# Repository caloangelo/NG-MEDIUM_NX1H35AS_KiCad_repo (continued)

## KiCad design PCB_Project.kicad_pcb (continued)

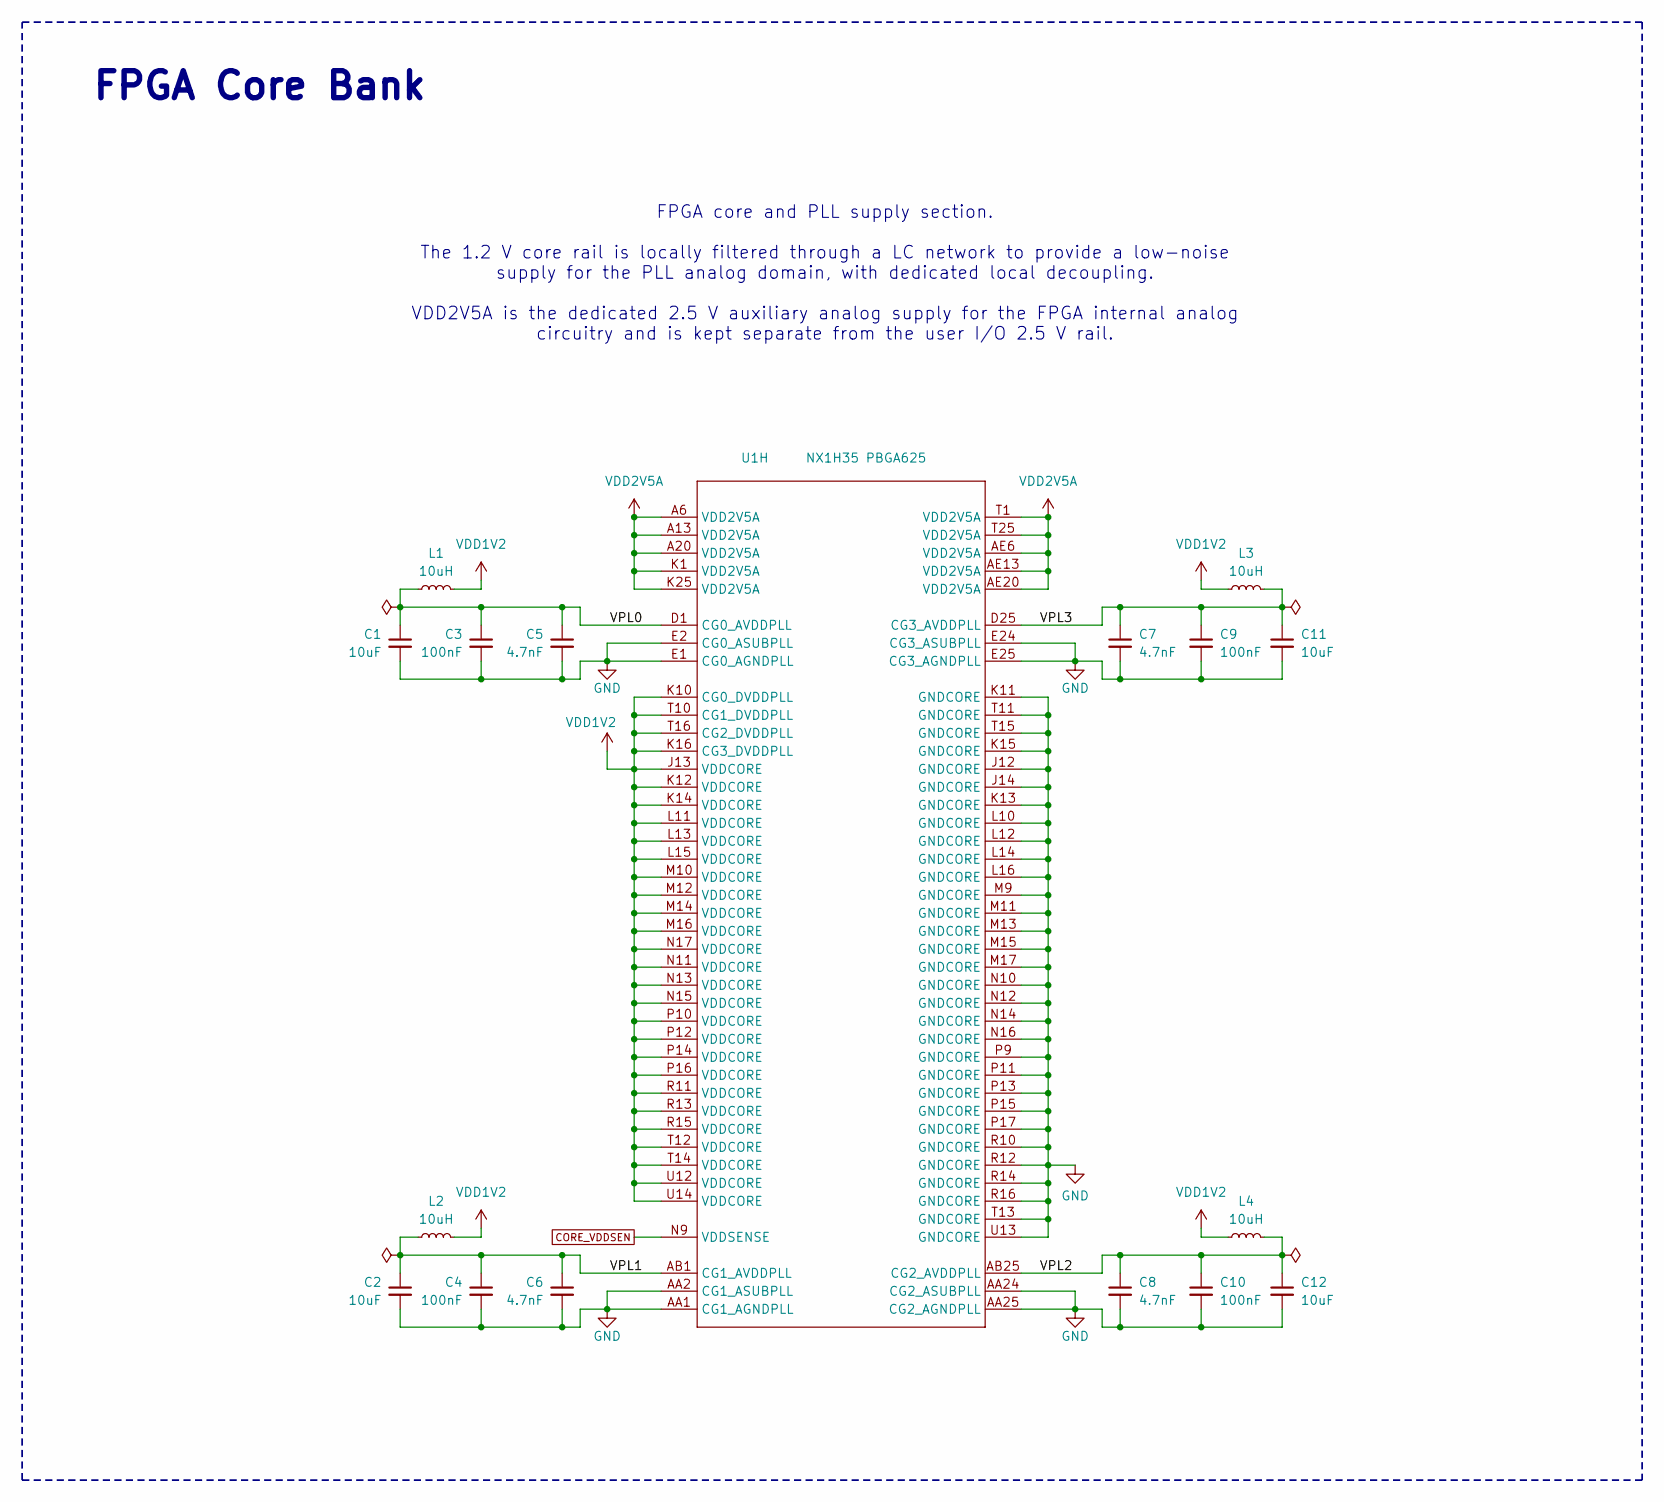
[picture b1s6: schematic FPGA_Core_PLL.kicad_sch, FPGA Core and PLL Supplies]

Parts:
C1, C2, C11, C12: 10uF; C_0603_1608Metric_Pad1.08x0.95mm_HandSolder
C3, C4, C9, C10: 100nF; C_0402_1005Metric_Pad0.74x0.62mm_HandSolder
C5, C6, C7, C8: 4.7nF; C_0402_1005Metric_Pad0.74x0.62mm_HandSolder
L1, L2, L3, L4: 10uH; L_0603_1608Metric_Pad1.05x0.95mm_HandSolder
U1: NX1H35 PBGA625; NX1H35S_CLGA625

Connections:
/FPGA_Core_PLL/VPL0: C1.1, C3.1, C5.1, L1.2, U1.D1 (CG0_AVDDPLL)
/FPGA_Core_PLL/VPL1: C2.1, C4.1, C6.1, L2.2, U1.AB1 (CG1_AVDDPLL)
/FPGA_Core_PLL/VPL2: C8.1, C10.1, C12.1, L4.2, U1.AB25 (CG2_AVDDPLL)
/FPGA_Core_PLL/VPL3: C7.1, C9.1, C11.1, L3.2, U1.D25 (CG3_AVDDPLL)
CORE_VDDSEN: U1.N9 (VDDSENSE); also elsewhere on the board
GND: C1.2, C2.2, C3.2, C4.2, C5.2, C6.2, C7.2, C8.2, C9.2, C10.2, C11.2, C12.2, U1.AA1 (CG1_AGNDPLL), U1.AA2 (CG1_ASUBPLL), U1.AA24 (CG2_ASUBPLL), U1.AA25 (CG2_AGNDPLL), U1.E1 (CG0_AGNDPLL), U1.E2 (CG0_ASUBPLL), U1.E24 (CG3_ASUBPLL), U1.E25 (CG3_AGNDPLL), U1.J12 (GNDCORE), U1.J14 (GNDCORE), U1.K11 (GNDCORE), U1.K13 (GNDCORE), U1.K15 (GNDCORE), U1.L10 (GNDCORE), U1.L12 (GNDCORE), U1.L14 (GNDCORE), U1.L16 (GNDCORE), U1.M9 (GNDCORE), U1.M11 (GNDCORE), U1.M13 (GNDCORE), U1.M15 (GNDCORE), U1.M17 (GNDCORE), U1.N10 (GNDCORE), U1.N12 (GNDCORE), U1.N14 (GNDCORE), U1.N16 (GNDCORE), U1.P9 (GNDCORE), U1.P11 (GNDCORE), U1.P13 (GNDCORE), U1.P15 (GNDCORE), U1.P17 (GNDCORE), U1.R10 (GNDCORE), U1.R12 (GNDCORE), U1.R14 (GNDCORE), U1.R16 (GNDCORE), U1.T11 (GNDCORE), U1.T13 (GNDCORE), U1.T15 (GNDCORE), U1.U13 (GNDCORE); also elsewhere on the board
VDD1V2: L1.1, L2.1, L3.1, L4.1, U1.J13 (VDDCORE), U1.K10 (CG0_DVDDPLL), U1.K12 (VDDCORE), U1.K14 (VDDCORE), U1.K16 (CG3_DVDDPLL), U1.L11 (VDDCORE), U1.L13 (VDDCORE), U1.L15 (VDDCORE), U1.M10 (VDDCORE), U1.M12 (VDDCORE), U1.M14 (VDDCORE), U1.M16 (VDDCORE), U1.N11 (VDDCORE), U1.N13 (VDDCORE), U1.N15 (VDDCORE), U1.N17 (VDDCORE), U1.P10 (VDDCORE), U1.P12 (VDDCORE), U1.P14 (VDDCORE), U1.P16 (VDDCORE), U1.R11 (VDDCORE), U1.R13 (VDDCORE), U1.R15 (VDDCORE), U1.T10 (CG1_DVDDPLL), U1.T12 (VDDCORE), U1.T14 (VDDCORE), U1.T16 (CG2_DVDDPLL), U1.U12 (VDDCORE), U1.U14 (VDDCORE); also elsewhere on the board
VDD2V5A: U1.A6 (VDD2V5A), U1.A13 (VDD2V5A), U1.A20 (VDD2V5A), U1.AE6 (VDD2V5A), U1.AE13 (VDD2V5A), U1.AE20 (VDD2V5A), U1.K1 (VDD2V5A), U1.K25 (VDD2V5A), U1.T1 (VDD2V5A), U1.T25 (VDD2V5A); also elsewhere on the board

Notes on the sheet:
FPGA Core Bank
FPGA core and PLL supply section. The 1.2 V core rail is locally filtered through a LC network to provide a low-noise supply for the PLL analog domain, with dedicated local decoupling. VDD2V5A is the dedicated 2.5 V auxiliary analog supply for the FPGA internal analog circuitry and is kept separate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

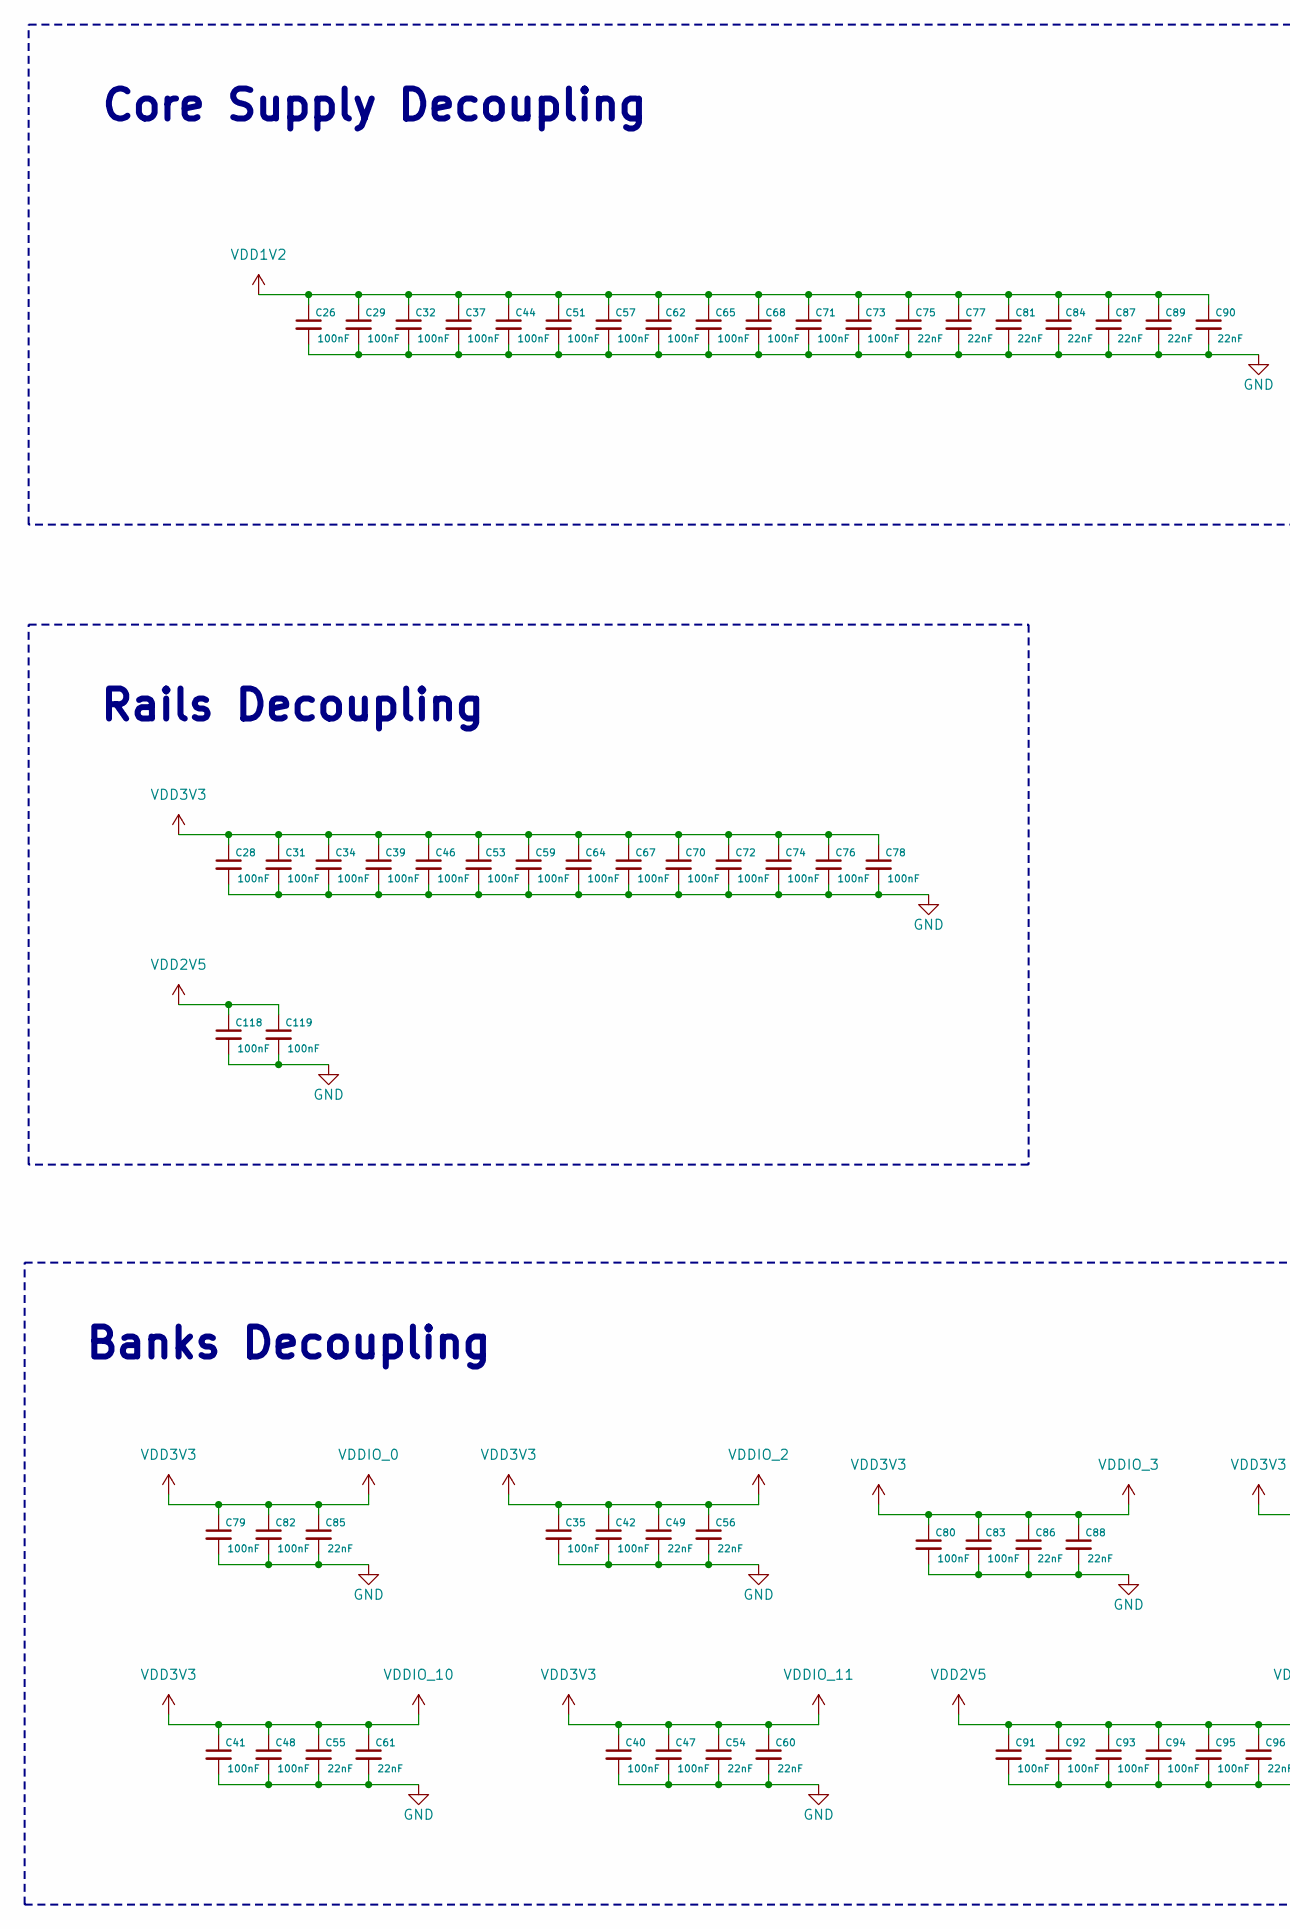
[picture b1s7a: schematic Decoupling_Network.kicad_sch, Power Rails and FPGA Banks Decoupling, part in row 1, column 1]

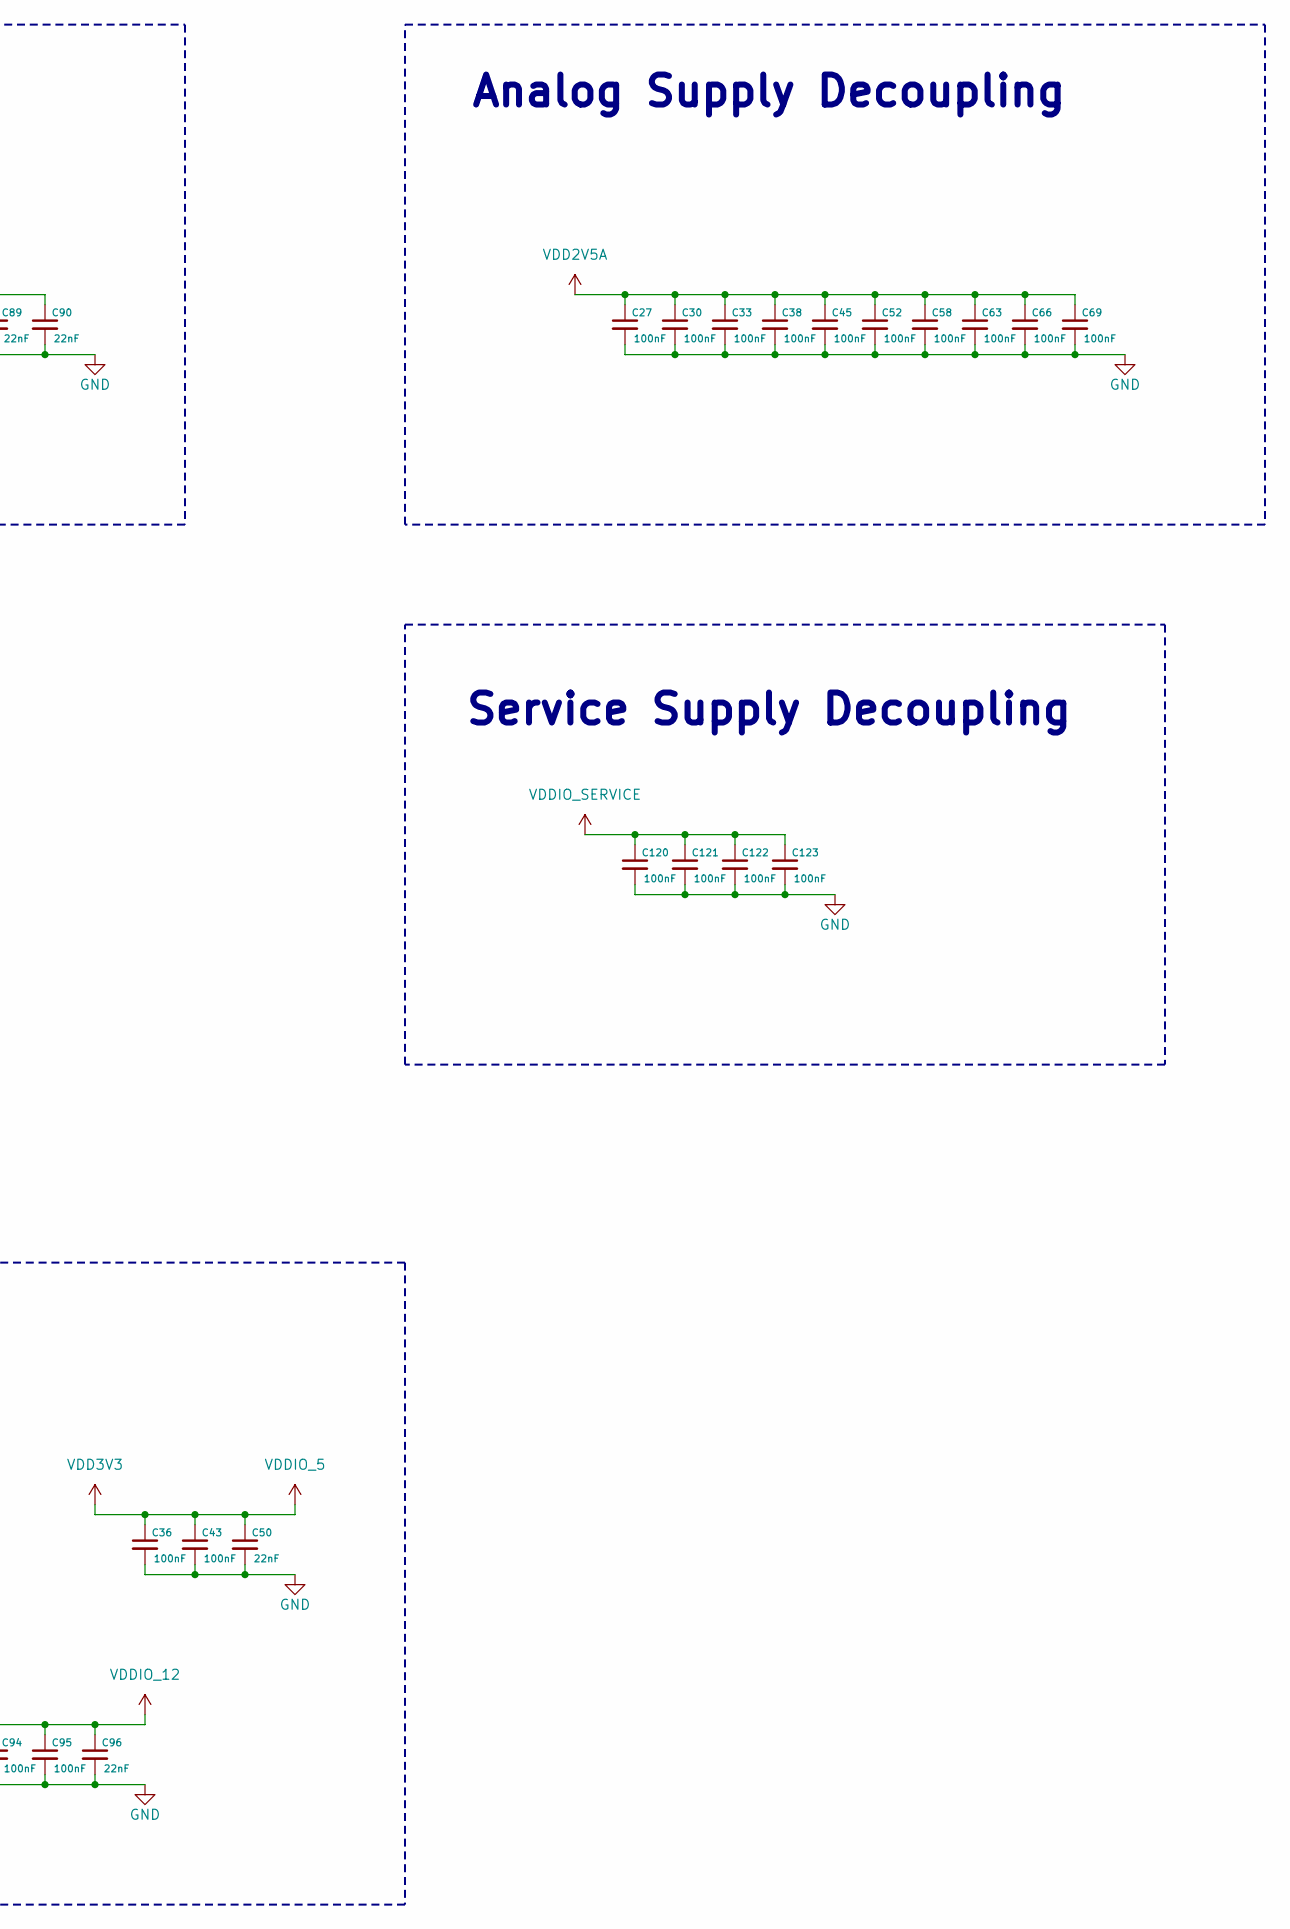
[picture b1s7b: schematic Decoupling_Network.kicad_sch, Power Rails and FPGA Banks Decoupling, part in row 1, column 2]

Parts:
C26, C27, C28, C29, C30, C31, C32, C33, C34, C35, C36, C37, C38, C39, C40, C41, C42, C43, C44, C45, C46, C47, C48, C51, C52, C53, C57, C58, C59, C62, C63, C64, C65, C66, C67, C68, C69, C70, C71, C72, C73, C74, C76, C78, C79, C80, C82, C83, C91, C92, C93, C94, C95, C118, C119, C120, C121, C122, C123: 100nF; C_0402_1005Metric_Pad0.74x0.62mm_HandSolder
C49, C50, C54, C55, C56, C60, C61, C75, C77, C81, C84, C85, C86, C87, C88, C89, C90, C96: 22nF; C_0402_1005Metric_Pad0.74x0.62mm_HandSolder

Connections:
GND: C26.2, C27.2, C28.2, C29.2, C30.2, C31.2, C32.2, C33.2, C34.2, C35.2, C36.2, C37.2, C38.2, C39.2, C40.2, C41.2, C42.2, C43.2, C44.2, C45.2, C46.2, C47.2, C48.2, C49.2, C50.2, C51.2, C52.2, C53.2, C54.2, C55.2, C56.2, C57.2, C58.2, C59.2, C60.2, C61.2, C62.2, C63.2, C64.2, C65.2, C66.2, C67.2, C68.2, C69.2, C70.2, C71.2, C72.2, C73.2, C74.2, C75.2, C76.2, C77.2, C78.2, C79.2, C80.2, C81.2, C82.2, C83.2, C84.2, C85.2, C86.2, C87.2, C88.2, C89.2, C90.2, C91.2, C92.2, C93.2, C94.2, C95.2, C96.2, C118.2, C119.2, C120.2, C121.2, C122.2, C123.2; also elsewhere on the board
VDD1V2: C26.1, C29.1, C32.1, C37.1, C44.1, C51.1, C57.1, C62.1, C65.1, C68.1, C71.1, C73.1, C75.1, C77.1, C81.1, C84.1, C87.1, C89.1, C90.1; also elsewhere on the board
VDD2V5: C91.1, C92.1, C93.1, C94.1, C95.1, C96.1, C118.1, C119.1; also elsewhere on the board
VDD2V5A: C27.1, C30.1, C33.1, C38.1, C45.1, C52.1, C58.1, C63.1, C66.1, C69.1; also elsewhere on the board
VDD3V3: C28.1, C31.1, C34.1, C35.1, C36.1, C39.1, C40.1, C41.1, C42.1, C43.1, C46.1, C47.1, C48.1, C49.1, C50.1, C53.1, C54.1, C55.1, C56.1, C59.1, C60.1, C61.1, C64.1, C67.1, C70.1, C72.1, C74.1, C76.1, C78.1, C79.1, C80.1, C82.1, C83.1, C85.1, C86.1, C88.1; also elsewhere on the board
VDDIO_SERVICE: C120.1, C121.1, C122.1, C123.1; also elsewhere on the board

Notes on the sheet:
Rails Decoupling
Core Supply Decoupling
Banks Decoupling
Service Supply Decoupling
Analog Supply Decoupling

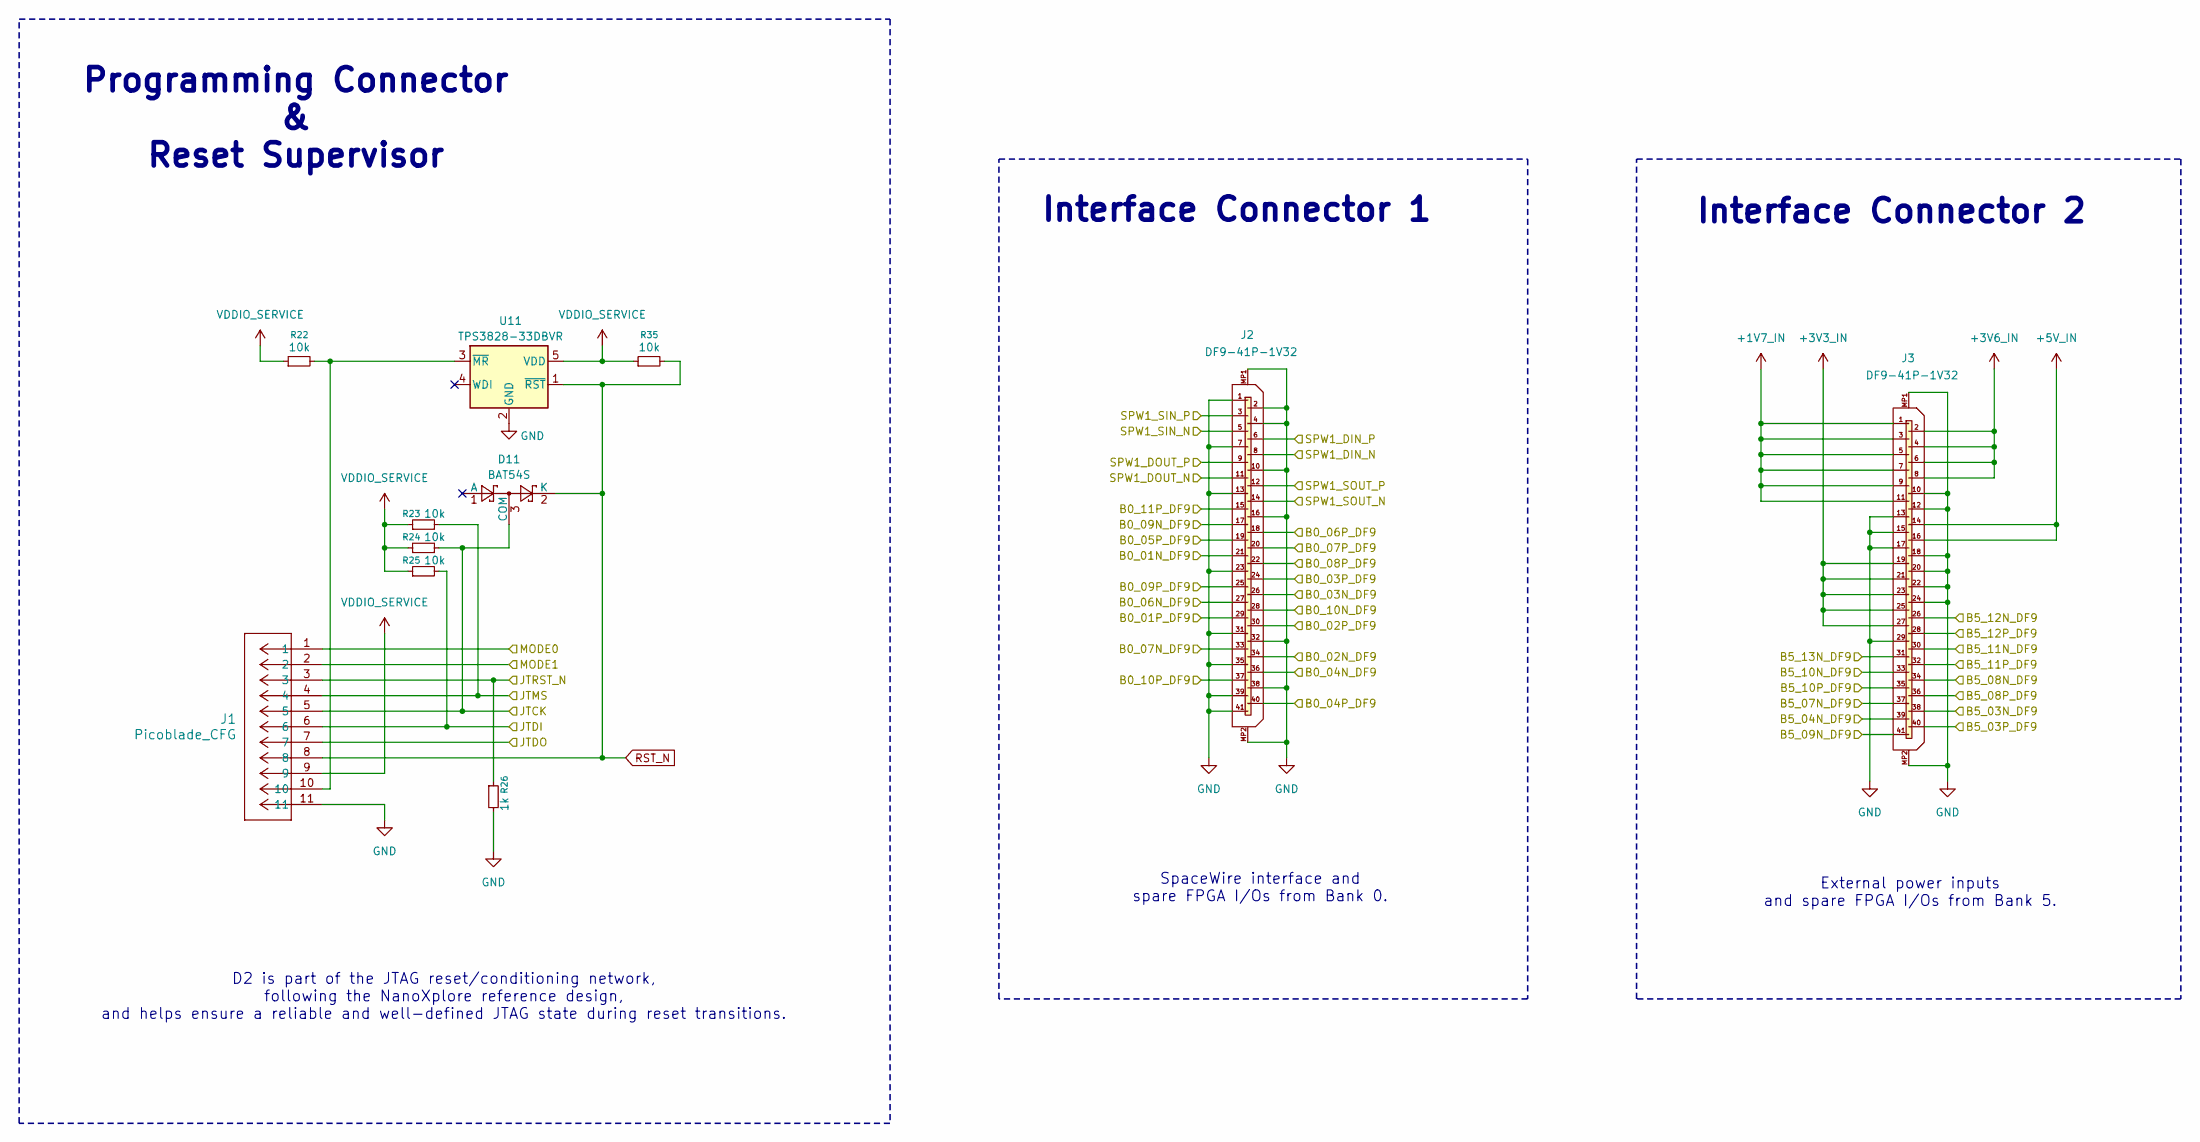
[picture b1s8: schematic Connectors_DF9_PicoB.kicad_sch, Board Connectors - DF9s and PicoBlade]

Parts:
D11: BAT54S; SOT-23
J1: Picoblade_CFG; CONN_532610001-SD_11_MOL
J2, J3: DF9-41P-1V32; DF941P1V32
R22, R23, R24, R25, R35: 10k; R_0402_1005Metric_Pad0.72x0.64mm_HandSolder
R26: 1k; R_0402_1005Metric_Pad0.72x0.64mm_HandSolder
U11: TPS3828-33DBVR; SOT-23-5_HandSoldering

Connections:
+1V7_IN: J3.1, J3.3, J3.5, J3.7, J3.9, J3.11; also elsewhere on the board
+3V3_IN: J3.19, J3.21, J3.23, J3.25, J3.27; also elsewhere on the board
+3V6_IN: J3.2, J3.4, J3.6, J3.8; also elsewhere on the board
+5V_IN: J3.14, J3.16; also elsewhere on the board
/Connectors_DF9_PicoB/B0_01N_DF9: J2.21; also elsewhere on the board
/Connectors_DF9_PicoB/B0_01P_DF9: J2.29; also elsewhere on the board
/Connectors_DF9_PicoB/B0_02N_DF9: J2.34; also elsewhere on the board
/Connectors_DF9_PicoB/B0_02P_DF9: J2.30; also elsewhere on the board
/Connectors_DF9_PicoB/B0_03N_DF9: J2.26; also elsewhere on the board
/Connectors_DF9_PicoB/B0_03P_DF9: J2.24; also elsewhere on the board
/Connectors_DF9_PicoB/B0_04N_DF9: J2.36; also elsewhere on the board
/Connectors_DF9_PicoB/B0_04P_DF9: J2.40; also elsewhere on the board
/Connectors_DF9_PicoB/B0_05P_DF9: J2.19; also elsewhere on the board
/Connectors_DF9_PicoB/B0_06N_DF9: J2.27; also elsewhere on the board
/Connectors_DF9_PicoB/B0_06P_DF9: J2.18; also elsewhere on the board
/Connectors_DF9_PicoB/B0_07N_DF9: J2.33; also elsewhere on the board
/Connectors_DF9_PicoB/B0_07P_DF9: J2.20; also elsewhere on the board
/Connectors_DF9_PicoB/B0_08P_DF9: J2.22; also elsewhere on the board
/Connectors_DF9_PicoB/B0_09N_DF9: J2.17; also elsewhere on the board
/Connectors_DF9_PicoB/B0_09P_DF9: J2.25; also elsewhere on the board
/Connectors_DF9_PicoB/B0_10N_DF9: J2.28; also elsewhere on the board
/Connectors_DF9_PicoB/B0_10P_DF9: J2.37; also elsewhere on the board
/Connectors_DF9_PicoB/B0_11P_DF9: J2.15; also elsewhere on the board
/Connectors_DF9_PicoB/B5_03N_DF9: J3.38; also elsewhere on the board
/Connectors_DF9_PicoB/B5_03P_DF9: J3.40; also elsewhere on the board
/Connectors_DF9_PicoB/B5_04N_DF9: J3.39; also elsewhere on the board
/Connectors_DF9_PicoB/B5_07N_DF9: J3.37; also elsewhere on the board
/Connectors_DF9_PicoB/B5_08N_DF9: J3.34; also elsewhere on the board
/Connectors_DF9_PicoB/B5_08P_DF9: J3.36; also elsewhere on the board
/Connectors_DF9_PicoB/B5_09N_DF9: J3.41; also elsewhere on the board
/Connectors_DF9_PicoB/B5_10N_DF9: J3.33; also elsewhere on the board
/Connectors_DF9_PicoB/B5_10P_DF9: J3.35; also elsewhere on the board
/Connectors_DF9_PicoB/B5_11N_DF9: J3.30; also elsewhere on the board
/Connectors_DF9_PicoB/B5_11P_DF9: J3.32; also elsewhere on the board
/Connectors_DF9_PicoB/B5_12N_DF9: J3.26; also elsewhere on the board
/Connectors_DF9_PicoB/B5_12P_DF9: J3.28; also elsewhere on the board
/Connectors_DF9_PicoB/B5_13N_DF9: J3.31; also elsewhere on the board
/Connectors_DF9_PicoB/JTCK: D11.3 (COM), J1.5, R24.2; also elsewhere on the board
/Connectors_DF9_PicoB/JTDI: J1.6, R25.2; also elsewhere on the board
/Connectors_DF9_PicoB/JTDO: J1.7; also elsewhere on the board
/Connectors_DF9_PicoB/JTMS: J1.4, R23.2; also elsewhere on the board
/Connectors_DF9_PicoB/JTRST_N: J1.3, R26.1; also elsewhere on the board
/Connectors_DF9_PicoB/MODE0: J1.1; also elsewhere on the board
/Connectors_DF9_PicoB/MODE1: J1.2; also elsewhere on the board
/Connectors_DF9_PicoB/SPW1_DIN_N: J2.8; also elsewhere on the board
/Connectors_DF9_PicoB/SPW1_DIN_P: J2.6; also elsewhere on the board
/Connectors_DF9_PicoB/SPW1_DOUT_N: J2.11; also elsewhere on the board
/Connectors_DF9_PicoB/SPW1_DOUT_P: J2.9; also elsewhere on the board
/Connectors_DF9_PicoB/SPW1_SIN_N: J2.5; also elsewhere on the board
/Connectors_DF9_PicoB/SPW1_SIN_P: J2.3; also elsewhere on the board
/Connectors_DF9_PicoB/SPW1_SOUT_N: J2.14; also elsewhere on the board
/Connectors_DF9_PicoB/SPW1_SOUT_P: J2.12; also elsewhere on the board
GND: J1.11, J2.1, J2.2, J2.4, J2.7, J2.10, J2.13, J2.16, J2.23, J2.31, J2.32, J2.35, J2.38, J2.39, J2.41, J2.MP1, J2.MP2, J3.10, J3.12, J3.13, J3.15, J3.17, J3.18, J3.20, J3.22, J3.24, J3.29, J3.MP1, J3.MP2, R26.2, U11.2 (GND); also elsewhere on the board
unnamed: J1.10, R22.2, U11.3 (~MR)
RST_N: D11.2 (K), J1.8, R35.2, U11.1 (~RST); also elsewhere on the board
VDDIO_SERVICE: J1.9, R22.1, R23.1, R24.1, R25.1, R35.1, U11.5 (VDD); also elsewhere on the board

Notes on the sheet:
SpaceWire interface and spare FPGA I/Os from Bank 0.
Interface Connector 2
External power inputs and spare FPGA I/Os from Bank 5.
Programming Connector & Reset Supervisor
Interface Connector 1
D2 is part of the JTAG reset/conditioning network, following the NanoXplore reference design, and helps ensure a reliable and well-defined JTAG state during reset transitions.

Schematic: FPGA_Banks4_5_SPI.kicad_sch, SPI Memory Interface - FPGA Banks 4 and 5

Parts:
C21, C22, C23: 100nF; C_0402_1005Metric_Pad0.74x0.62mm_HandSolder
D7, D8, D9, D10: LED_green; LED_0603_1608Metric
R12, R13, R14, R15: 1k; R_0402_1005Metric_Pad0.72x0.64mm_HandSolder
R16, R17, R18: 100k; R_0402_1005Metric_Pad0.72x0.64mm_HandSolder
U1: NX1H35 PBGA625; NX1H35S_CLGA625
U5, U6, U7: CY15B108QN-40SXI; SOIC8_001-85261_CYP

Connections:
/Connectors_DF9_PicoB/B5_03N_DF9: U1.AA23 (IO_B5D03N_DQS_SWDI); also elsewhere on the board
/Connectors_DF9_PicoB/B5_03P_DF9: U1.AB23 (IO_B5D03P_DQS_SWDI); also elsewhere on the board
/Connectors_DF9_PicoB/B5_04N_DF9: U1.AA22 (IO_B5D04N_DQ_SWSI); also elsewhere on the board
/Connectors_DF9_PicoB/B5_07N_DF9: U1.AA21 (IO_B5D07N); also elsewhere on the board
/Connectors_DF9_PicoB/B5_08N_DF9: U1.Y20 (IO_B5D08N); also elsewhere on the board
/Connectors_DF9_PicoB/B5_08P_DF9: U1.Y21 (IO_B5D08P_CLK0); also elsewhere on the board
/Connectors_DF9_PicoB/B5_09N_DF9: U1.AB20 (IO_B5D09N); also elsewhere on the board
/Connectors_DF9_PicoB/B5_10N_DF9: U1.AA19 (IO_B5D10N_DQ); also elsewhere on the board
/Connectors_DF9_PicoB/B5_10P_DF9: U1.AA20 (IO_B5D10P); also elsewhere on the board
/Connectors_DF9_PicoB/B5_11N_DF9: U1.W19 (IO_B5D11N_DQ); also elsewhere on the board
/Connectors_DF9_PicoB/B5_11P_DF9: U1.Y19 (IO_B5D11P_DQ); also elsewhere on the board
/Connectors_DF9_PicoB/B5_12N_DF9: U1.V18 (IO_B5D12N_DQ_SWDO); also elsewhere on the board
/Connectors_DF9_PicoB/B5_12P_DF9: U1.W18 (IO_B5D12P_DQ_SWDO); also elsewhere on the board
/Connectors_DF9_PicoB/B5_13N_DF9: U1.Y18 (IO_B5D13N_DQS_SWSO); also elsewhere on the board
/FPGA_Banks4_5_SPI/FRAM1_CLK: U1.AC21 (IO_B5D06N_CAL), U5.6 (SCK)
/FPGA_Banks4_5_SPI/FRAM1_CS_N: R16.2, U1.AE25 (IO_B5D01P_DQ_SWDO), U5.1 (~CS)
/FPGA_Banks4_5_SPI/FRAM1_MISO: U1.AC24 (IO_B5D02N_DQ_SWSO), U5.2 (SO)
/FPGA_Banks4_5_SPI/FRAM1_MOSI: U1.AE22 (IO_B5D05P_DQ), U5.5 (SI)
/FPGA_Banks4_5_SPI/FRAM2_CLK: U1.AC23 (IO_B5D02P_DQ_SWSO), U6.6 (SCK)
/FPGA_Banks4_5_SPI/FRAM2_CS_N: R17.2, U1.AD25 (IO_B5D01N_DQ_SWDO), U6.1 (~CS)
/FPGA_Banks4_5_SPI/FRAM2_MISO: U1.AC20 (IO_B5D09P_CLK1), U6.2 (SO)
/FPGA_Banks4_5_SPI/FRAM2_MOSI: U1.AD22 (IO_B5D05N_DQ), U6.5 (SI)
/FPGA_Banks4_5_SPI/FRAM_RO_CLK: U1.Y17 (IO_B5D14P_DQ_SWDI), U7.6 (SCK)
/FPGA_Banks4_5_SPI/FRAM_RO_CS_N: R18.2, U1.AA18 (IO_B5D13P_DQS_SWSO), U7.1 (~CS)
/FPGA_Banks4_5_SPI/FRAM_RO_MISO: U1.AC19 (IO_B5D15P_DQ_SWSI), U7.2 (SO)
/FPGA_Banks4_5_SPI/FRAM_RO_MOSI: U1.AC22 (IO_B5D06P_DQ), U7.5 (SI)
/FPGA_Banks4_5_SPI/LD_USER1: R12.1, U1.W17 (IO_B5D14N_DQ_SWDI)
/FPGA_Banks4_5_SPI/LD_USER2: R13.1, U1.AB21 (IO_B5D07P)
/FPGA_Banks4_5_SPI/LD_USER3: R14.1, U1.AB22 (IO_B5D04P_DQ_SWSI)
/FPGA_Banks4_5_SPI/LD_USER4: R15.1, U1.AB19 (IO_B5D15N_DQ_SWSI)
GND: C21.2, C22.2, C23.2, D7.2 (A), D8.2 (A), D9.2 (A), D10.2 (A), U1.AA14 (GNDIO_4), U1.AB14 (VDDIO_4), U1.AB24 (GNDIO_5), U1.AD16 (GNDIO_4), U1.AD18 (VTO_4), U1.AD19 (VDDIO_4), U1.AD20 (GNDIO_5), U1.AD23 (GNDIO_5), U1.AE14 (VTO_4), U1.AE16 (VDDS_4), U1.AE17 (VDDIO_4), U1.AE19 (GNDIO_4), U1.AE23 (VDDS_5), U1.U17 (GNDIO_5), U1.W14 (GNDIO_4), U1.Y14 (VDDIO_4), U5.4 (GND), U6.4 (GND), U7.4 (GND); also elsewhere on the board
unnamed: D7.1 (K), R12.2
unnamed: D8.1 (K), R13.2
unnamed: D9.1 (K), R14.2
unnamed: D10.1 (K), R15.2
VDD3V3: C21.1, C22.1, C23.1, R16.1, R17.1, R18.1, U1.AC25 (VDDIO_5), U1.AE21 (VDDIO_5), U1.AE24 (VDDIO_5), U1.V17 (VDDIO_5), U5.3 (~WP), U5.8 (VDD), U6.3 (~WP), U6.8 (VDD), U7.3 (~WP), U7.8 (VDD); also elsewhere on the board

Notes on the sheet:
Treated as read-only at software level. Stores the Stage-0 bootloader image and golden recovery images.
Bank 4: unused
LEDs
Non-volatile memory used for persistent storage across power cycles
Bank 5: SPI memory interface (FRAMs) and spare I/Os routed to DF9
FPGA Bank 4 and 5
FRAMs 1 and 2
FRAM RO

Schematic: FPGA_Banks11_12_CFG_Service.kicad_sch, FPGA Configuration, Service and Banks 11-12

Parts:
C13, C14, C97: 100nF; C_0402_1005Metric_Pad0.74x0.62mm_HandSolder
D1, D2, D3, D4, D6: LED_green; LED_0603_1608Metric
D5: LED_red; LED_0603_1608Metric
L5: 10uH; L_0603_1608Metric_Pad1.05x0.95mm_HandSolder
R1, R2, R6, R7, R8, R9, R10, R11: 1k; R_0402_1005Metric_Pad0.72x0.64mm_HandSolder
R3, R4: 10k; R_0402_1005Metric_Pad0.72x0.64mm_HandSolder
R5: 100k; R_0402_1005Metric_Pad0.72x0.64mm_HandSolder
U1: NX1H35 PBGA625; NX1H35S_CLGA625
U2: M95P32-IXMNT/E; SO8N_4X5X1P27_STM
Y1: LFSPXO025225_25MHz; SON4_LFSPXO025225_IQD-M

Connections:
/Connectors_DF9_PicoB/JTCK: U1.M5 (TCK); also elsewhere on the board
/Connectors_DF9_PicoB/JTDI: U1.M1 (TDI); also elsewhere on the board
/Connectors_DF9_PicoB/JTDO: U1.N3 (TDO); also elsewhere on the board
/Connectors_DF9_PicoB/JTMS: U1.M2 (TMS); also elsewhere on the board
/Connectors_DF9_PicoB/JTRST_N: U1.M4 (TRST); also elsewhere on the board
/Connectors_DF9_PicoB/MODE0: R1.2, U1.L8 (MODE0); also elsewhere on the board
/Connectors_DF9_PicoB/MODE1: R2.1, U1.L7 (MODE1); also elsewhere on the board
/Connectors_DF9_PicoB/SPW1_DIN_N: U1.E4 (IO_B12D03N_DQS_SWDI); also elsewhere on the board
/Connectors_DF9_PicoB/SPW1_DIN_P: U1.D3 (IO_B12D03P_DQS_SWDI); also elsewhere on the board
/Connectors_DF9_PicoB/SPW1_DOUT_N: U1.F4 (IO_B12D01N_DQ_SWDO); also elsewhere on the board
/Connectors_DF9_PicoB/SPW1_DOUT_P: U1.E3 (IO_B12D01P_DQ_SWDO); also elsewhere on the board
/Connectors_DF9_PicoB/SPW1_SIN_N: U1.B1 (IO_B12D04N_DQ_SWSI); also elsewhere on the board
/Connectors_DF9_PicoB/SPW1_SIN_P: U1.A1 (IO_B12D04P_DQ_SWSI); also elsewhere on the board
/Connectors_DF9_PicoB/SPW1_SOUT_N: U1.F6 (IO_B12D02N_DQ_SWSO); also elsewhere on the board
/Connectors_DF9_PicoB/SPW1_SOUT_P: U1.F5 (IO_B12D02P_DQ_SWSO); also elsewhere on the board
/FPGA_Banks11_12_CFG_Service/CFG_EEPROM_CLK: U1.P7 (D9), U2.6 (SCK)
/FPGA_Banks11_12_CFG_Service/CFG_EEPROM_CS_N: R5.2, U1.P8 (D8), U2.1 (~CS)
/FPGA_Banks11_12_CFG_Service/CFG_EEPROM_MISO: U1.P6 (D10), U2.2 (MISO)
/FPGA_Banks11_12_CFG_Service/CFG_EEPROM_MOSI: U1.R8 (D11), U2.5 (MOSI)
/FPGA_Banks11_12_CFG_Service/LD_CFG0: R6.1, U1.R7 (D12)
/FPGA_Banks11_12_CFG_Service/LD_CFG1: R7.1, U1.R6 (D13)
/FPGA_Banks11_12_CFG_Service/LD_CFG2: R8.1, U1.T6 (D14)
/FPGA_Banks11_12_CFG_Service/LD_CFG3: R9.1, U1.T5 (D15)
/FPGA_Banks11_12_CFG_Service/OSC0: U1.E6 (IO_B12D09P_CLK1), Y1.3 (OUT)
/FPGA_Banks11_12_CFG_Service/PERR: R10.1, U1.N7 (ERROR)
/FPGA_Banks11_12_CFG_Service/PRDY: R11.1, U1.N6 (READY)
/FPGA_Banks11_12_CFG_Service/SDRAM_B_A4: U1.A11 (IO_B11D09P); also elsewhere on the board
/FPGA_Banks11_12_CFG_Service/SDRAM_B_A5: U1.B11 (IO_B11D09N); also elsewhere on the board
/FPGA_Banks11_12_CFG_Service/SDRAM_B_A6: U1.B12 (IO_B11D13P_DQS_SWSO); also elsewhere on the board
/FPGA_Banks11_12_CFG_Service/SDRAM_B_A7: U1.C10 (IO_B11D08N); also elsewhere on the board
/FPGA_Banks11_12_CFG_Service/SDRAM_B_A8: U1.B9 (IO_B11D05N_DQ); also elsewhere on the board
/FPGA_Banks11_12_CFG_Service/SDRAM_B_A9: U1.C12 (IO_B11D13N_DQS_SWSO); also elsewhere on the board
/FPGA_Banks11_12_CFG_Service/SDRAM_B_A11: U1.D10 (IO_B11D07P); also elsewhere on the board
/FPGA_Banks11_12_CFG_Service/SDRAM_B_CKE: U1.E11 (IO_B11D10N_DQ); also elsewhere on the board
/FPGA_Banks11_12_CFG_Service/SDRAM_B_CLK: U1.D9 (IO_B11D06N_CAL); also elsewhere on the board
/FPGA_Banks11_12_CFG_Service/SDRAM_B_DQ8: U1.C8 (IO_B11D03P_DQS_SWDI); also elsewhere on the board
/FPGA_Banks11_12_CFG_Service/SDRAM_B_DQ9: U1.C9 (IO_B11D06P_DQ); also elsewhere on the board
/FPGA_Banks11_12_CFG_Service/SDRAM_B_DQ10: U1.D8 (IO_B11D03N_DQS_SWDI); also elsewhere on the board
/FPGA_Banks11_12_CFG_Service/SDRAM_B_DQ11: U1.C11 (IO_B11D08P); also elsewhere on the board
/FPGA_Banks11_12_CFG_Service/SDRAM_B_DQ12: U1.E9 (IO_B11D04P_DQ_SWSI); also elsewhere on the board
/FPGA_Banks11_12_CFG_Service/SDRAM_B_DQ13: U1.D11 (IO_B11D10P); also elsewhere on the board
/FPGA_Banks11_12_CFG_Service/SDRAM_B_DQ14: U1.E10 (IO_B11D07N); also elsewhere on the board
/FPGA_Banks11_12_CFG_Service/SDRAM_B_DQ15: U1.D13 (IO_B11D14P_DQ_SWDI); also elsewhere on the board
/FPGA_Banks11_12_CFG_Service/SDRAM_B_UDQM: U1.A8 (IO_B11D05P_DQ); also elsewhere on the board
/FPGA_Banks11_12_CFG_Service/VDDS_12: C97.1, L5.1, U1.A3 (VDDS_12)
GND: C13.2, C14.2, C97.2, D1.1 (K), D2.1 (K), D3.1 (K), D4.1 (K), D5.1 (K), D6.1 (K), R1.1, U1.A7 (GNDIO_11), U1.A10 (VDDS_11), U1.B3 (GNDIO_12), U1.B6 (GNDIO_12), U1.B10 (GNDIO_11), U1.C13 (GNDIO_11), U1.D2 (GNDIO_12), U1.E12 (GNDIO_11), U1.J10 (GNDIO_12), U1.K2 (GNDLVDS), U1.L1 (VDDLVDS), U1.M6 (GNDIO_SERVICE), U1.M8 (MODE2), U1.N2 (GNDIO_SERVICE), U1.N4 (GNDIO_SERVICE), U1.N8 (MODE3), U1.T2 (GNDIO_SERVICE), U1.T20 (VDDIO_6), U1.T21 (GNDIO_6), U1.T23 (GNDIO_6), U1.T24 (VDDIO_6), U1.Y24 (GNDIO_6), U1.Y25 (VDDIO_6), U2.4 (GND), Y1.2 (GND); also elsewhere on the board
unnamed: D1.2 (A), R6.2
unnamed: D2.2 (A), R7.2
unnamed: D3.2 (A), R8.2
unnamed: D4.2 (A), R9.2
unnamed: D5.2 (A), R10.2
unnamed: D6.2 (A), R11.2
unnamed: R3.1, U1.M3 (CLK)
unnamed: R4.2, U2.3 (~WP), U2.7 (~HOLD)
RST_N: U1.L6 (RST_N); also elsewhere on the board
VDD2V5: C14.1, L5.2, U1.A2 (VDDIO_12), U1.A5 (VDDIO_12), U1.C1 (VDDIO_12), U1.J9 (VDDIO_12), Y1.4 (VDD); also elsewhere on the board
VDD3V3: U1.A9 (VDDIO_11), U1.B7 (VDDIO_11), U1.D12 (VDDIO_11), U1.F12 (VDDIO_11); also elsewhere on the board
VDDIO_SERVICE: C13.1, R2.2, R3.2, R4.1, R5.1, U1.M7 (VDDIO_SERVICE), U1.N1 (VDDIO_SERVICE), U1.N5 (VDDIO_SERVICE), U1.R1 (VDDIO_SERVICE), U2.8 (VCC); also elsewhere on the board

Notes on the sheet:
Bank SERVICE: dedicated to FPGA configuration, programming, reset, and service interfaces.
Bank 12: connected to the SpaceWire interface and the 25 MHz oscillator clock input.
Oscillator
Stores the FPGA configuration bitstream. Used during power-up for Master SPI configuration.
Bank 11: connected to the secondary BGA SDRAM interface.
25MHz oscillator used for system clock.
CFG EEPROM
FPGA Banks 6 and SERVICE
LEDs
Bank 6: unused
FPGA Banks 11 and 12
Visual indicators for the PRDY and PERR programming/status signals.
